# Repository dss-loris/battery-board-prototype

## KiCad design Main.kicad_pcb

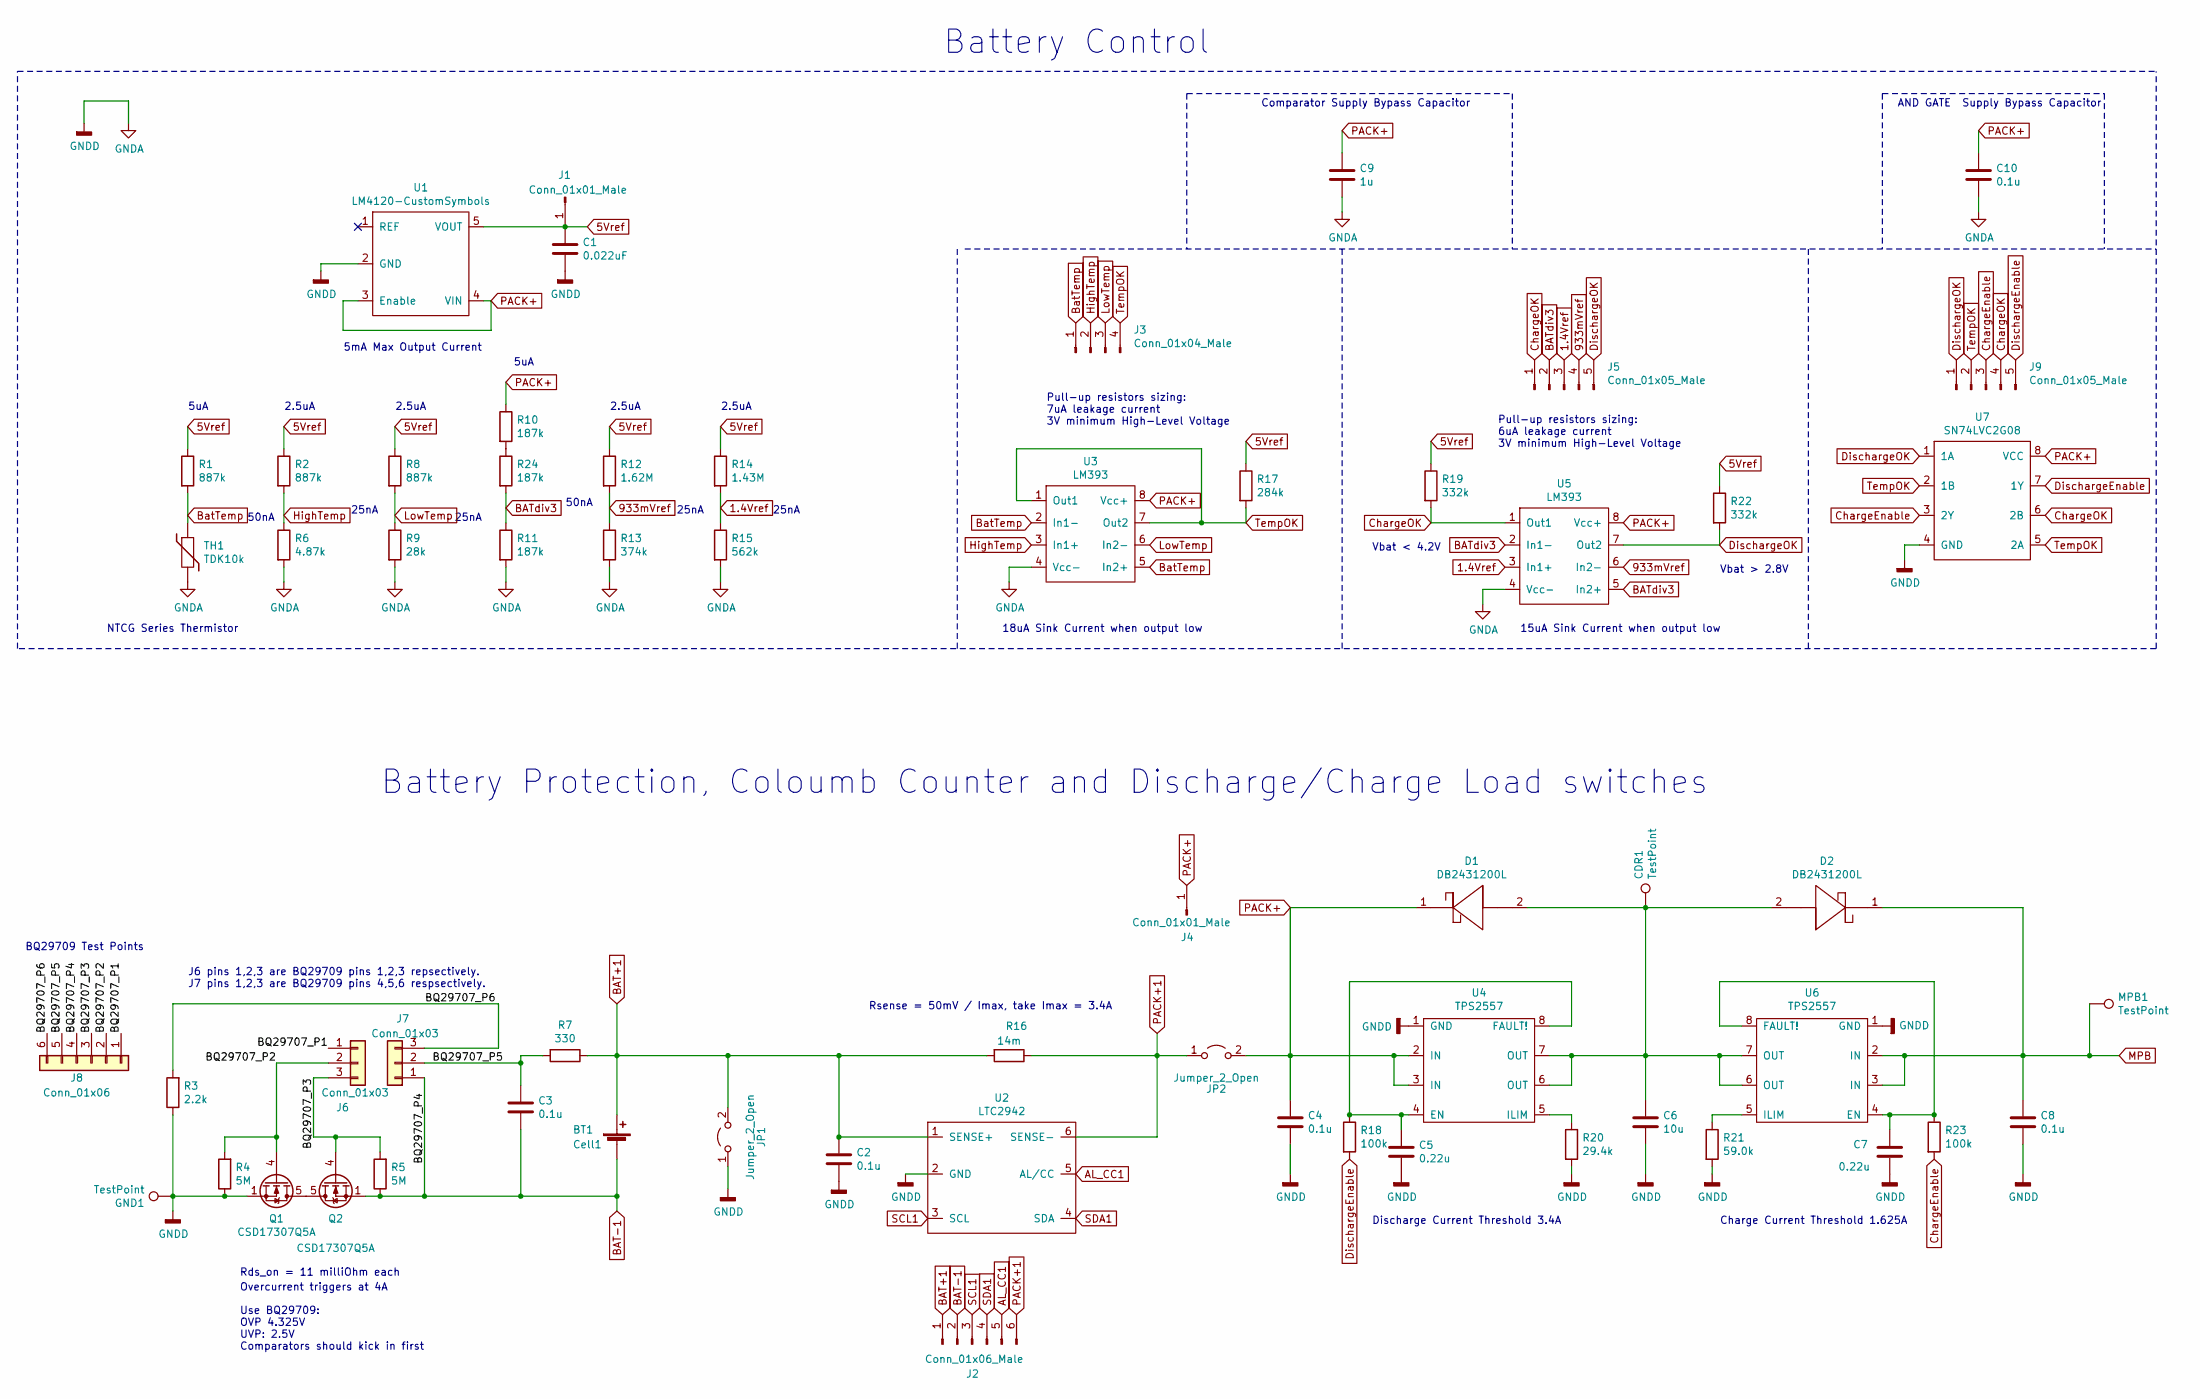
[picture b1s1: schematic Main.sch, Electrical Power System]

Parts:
BT1: Cell1; BatteryHolder_Keystone_1042_1x18650
C1: 0.022uF; C_1206_3216Metric_Pad1.42x1.75mm_HandSolder
C2, C3, C4, C8, C10: 0.1u; C_1206_3216Metric_Pad1.42x1.75mm_HandSolder
C5, C7: 0.22u; C_1206_3216Metric_Pad1.42x1.75mm_HandSolder
C6: 10u; C_1206_3216Metric_Pad1.42x1.75mm_HandSolder
C9: 1u; C_1206_3216Metric_Pad1.42x1.75mm_HandSolder
CDR1: TestPoint; PinHeader_1x01_P2.00mm_Vertical
D1, D2: DB2431200L
GND1: TestPoint; PinHeader_1x01_P2.00mm_Vertical
J1, J4: Conn_01x01_Male; PinHeader_1x01_P2.00mm_Vertical
J2: Conn_01x06_Male; PinSocket_1x06_P2.00mm_Vertical
J3: Conn_01x04_Male; PinHeader_1x04_P2.00mm_Vertical
J5, J9: Conn_01x05_Male; PinHeader_1x05_P2.00mm_Vertical
J6, J7: Conn_01x03; PinSocket_1x03_P2.54mm_Vertical
J8: Conn_01x06; PinHeader_1x06_P2.00mm_Vertical
JP1, JP2: Jumper_2_Open; PinSocket_1x01_P2.54mm_Vertical
MPB1: TestPoint; PinHeader_1x01_P2.00mm_Vertical
Q1, Q2: CSD17307Q5A; TDSON-8-1
R1, R2, R8: 887k; R_1206_3216Metric_Pad1.42x1.75mm_HandSolder
R3: 2.2k; R_1206_3216Metric_Pad1.42x1.75mm_HandSolder
R4, R5: 5M; R_1206_3216Metric_Pad1.42x1.75mm_HandSolder
R6: 4.87k; R_1206_3216Metric_Pad1.42x1.75mm_HandSolder
R7: 330; R_1206_3216Metric_Pad1.42x1.75mm_HandSolder
R9: 28k; R_1206_3216Metric_Pad1.42x1.75mm_HandSolder
R10, R11, R24: 187k; R_1206_3216Metric_Pad1.42x1.75mm_HandSolder
R12: 1.62M; R_1206_3216Metric_Pad1.42x1.75mm_HandSolder
R13: 374k; R_1206_3216Metric_Pad1.42x1.75mm_HandSolder
R14: 1.43M; R_0805_2012Metric_Pad1.15x1.40mm_HandSolder
R15: 562k; R_1206_3216Metric_Pad1.42x1.75mm_HandSolder
R16: 14m; R_0805_2012Metric
R17: 284k; R_0603_1608Metric_Pad1.05x0.95mm_HandSolder
R18, R23: 100k; R_1206_3216Metric_Pad1.42x1.75mm_HandSolder
R19, R22: 332k; R_1206_3216Metric_Pad1.42x1.75mm_HandSolder
R20: 29.4k; R_1206_3216Metric_Pad1.42x1.75mm_HandSolder
R21: 59.0k; R_1206_3216Metric_Pad1.42x1.75mm_HandSolder
TH1: TDK10k; R_0402_1005Metric
U1: LM4120-CustomSymbols; SOT-23-5_HandSoldering
U2: LTC2942; DFN-6-1EP_3x2mm_P0.5mm_EP1.65x1.35mm
U3, U5: LM393; SOIC-8-1EP_3.9x4.9mm_P1.27mm_EP2.29x3mm
U4, U6: TPS2557
U7: SN74LVC2G08; SN74LVC2G08DCTR

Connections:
1.4Vref: J5.3, R14.2, R15.1, U5.3 (In1+)
5Vref: C1.1, J1.1, R1.1, R2.1, R8.1, R12.1, R14.1, R17.1, R19.1, R22.1, U1.5 (VOUT)
933mVref: J5.4, R12.2, R13.1, U5.6 (In2-)
/BQ29707_P1: J6.1, J8.1
/BQ29707_P2: J6.2, J8.2, Q1.4 (G), R4.2
/BQ29707_P3: J6.3, J8.3, Q2.4 (G), R5.2
/BQ29707_P5: C3.1, J7.2, J8.5, R7.2
/BQ29707_P6: J7.3, J8.6, R3.2
AL_CC1: J2.5, U2.5 (AL/CC)
BAT+1: BT1.1 (+), C2.1, J2.1, JP1.2 (B), R7.1, R16.2, U2.1 (SENSE+)
BAT-1: BT1.2 (-), C3.2, J2.2, J7.1, J8.4, Q2.1 (S), Q2.2 (S), Q2.3 (S), R5.1
BATdiv3: J5.2, R11.1, R24.2, U5.2 (In1-), U5.5 (In2+)
BatTemp: J3.1, R1.2, TH1.1, U3.2 (In1-), U3.5 (In2+)
ChargeEnable: J9.3, R23.2, U7.3 (2Y)
ChargeOK: J5.1, J9.4, R19.2, U5.1 (Out1), U7.6 (2B)
DischargeEnable: J9.5, R18.2, U7.7 (1Y)
DischargeOK: J5.5, J9.1, R22.2, U5.7 (Out2), U7.1 (1A)
GNDA: C1.2, C2.2, C4.2, C5.2, C6.2, C7.2, C8.2, C9.2, C10.2, GND1.1, JP1.1 (A), Q1.1 (S), Q1.2 (S), Q1.3 (S), R3.1, R4.1, R6.2, R9.2, R11.2, R13.2, R15.2, R20.2, R21.2, TH1.2, U1.2 (GND), U2.2 (GND), U3.4 (Vcc-), U4.1 (GND), U5.4 (Vcc-), U6.1 (GND), U7.4 (GND)
HighTemp: J3.2, R2.2, R6.1, U3.3 (In1+)
LowTemp: J3.3, R8.2, R9.1, U3.6 (In2-)
MPB: C8.1, D2.1, MPB1.1, U6.2 (IN), U6.3 (IN)
unnamed: C5.1, R18.1, U4.4 (EN), U4.8 (FAULT!)
unnamed: C6.1, CDR1.1, D1.2, D2.2, U4.6 (OUT), U4.7 (OUT), U6.6 (OUT), U6.7 (OUT)
unnamed: C7.1, R23.1, U6.4 (EN), U6.8 (FAULT!)
unnamed: Q1.5 (D), Q2.5 (D)
unnamed: R10.2, R24.1
unnamed: R20.1, U4.5 (ILIM)
unnamed: R21.1, U6.5 (ILIM)
PACK+: C4.1, C9.1, C10.1, D1.1, J4.1, JP2.2 (B), R10.1, U1.3 (Enable), U1.4 (VIN), U3.8 (Vcc+), U4.2 (IN), U4.3 (IN), U5.8 (Vcc+), U7.8 (VCC)
PACK+1: J2.6, JP2.1 (A), R16.1, U2.6 (SENSE-)
SCL1: J2.3, U2.3 (SCL)
SDA1: J2.4, U2.4 (SDA)
TempOK: J3.4, J9.2, R17.2, U3.1 (Out1), U3.7 (Out2), U7.2 (1B), U7.5 (2A)

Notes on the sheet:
Rds_on = 11 milliOhm each
Overcurrent triggers at 4A
Discharge Current Threshold 3.4A
Charge Current Threshold 1.625A
2.5uA
5uA
25nA
50nA
5mA Max Output Current
NTCG Series Thermistor
Vbat > 2.8V
Vbat < 4.2V
Use BQ29709: OVP 4.325V UVP: 2.5V Comparators should kick in first
Pull-up resistors sizing: 6uA leakage current 3V minimum High-Level Voltage
Pull-up resistors sizing: 7uA leakage current 3V minimum High-Level Voltage
18uA Sink Current when output low
15uA Sink Current when output low
Comparator Supply Bypass Capacitor
AND GATE Supply Bypass Capacitor
Battery Control
Battery Protection, Coloumb Counter and Discharge/Charge Load switches
BQ29709 Test Points
Rsense = 50mV / Imax, take Imax = 3.4A
J6 pins 1,2,3 are BQ29709 pins 1,2,3 repsectively. J7 pins 1,2,3 are BQ29709 pins 4,5,6 respsectively.

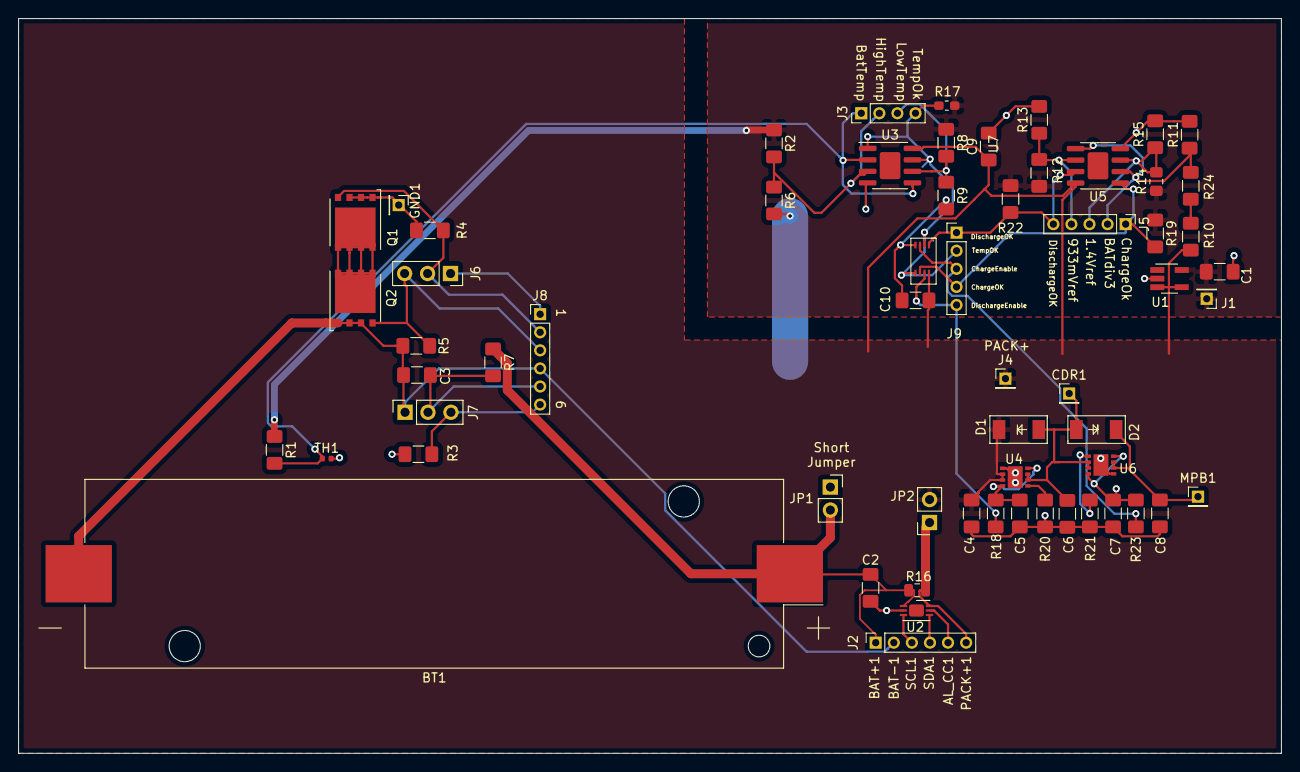
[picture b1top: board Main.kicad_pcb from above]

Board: 2 copper layers, 139.7 x 81.3 mm, 61 parts (0 on the bottom side), 33 nets.

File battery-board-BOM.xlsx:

Index | Quantity | Part Number | Manufacturer Part Number | Description | Customer Reference | Available | Backorder | Unit Price | Extended Price USD
1 | 4 | DB2431200LCT-ND | DB2431200L | DIODE SCHOTTKY 30V 5A TMINIP2 | D1,D2 … BB | 4 | 0 | 0.42 | 1.68
2 | 2 | 2057-2PH1-05-UA-ND | 2PH1-05-UA | CONN HEADER VERT 5POS 2MM | J5,J9 … BB | 2 | 0 | 0.18 | 0.36
3 | 2 | 2057-2PH1-04-UA-ND | 2PH1-04-UA | CONN HEADER VERT 4POS 2MM | J3 … BB | 2 | 0 | 0.14000000000000001 | 0.28000000000000003
4 | 2 | 952-1316-ND | M22-2511005 | CONN HEADER VERT 10POS 2MM | J1,J4,CDR1,GND1,MPB1 … BB | 2 | 0 | 0.61 | 1.22
5 | 2 | LM4120AIM5-5.0/NOPBCT-ND | LM4120AIM5-5.0/NOPB | IC VREF SERIES 0.2% SOT23-5 | U1 … BB | 2 | 0 | 2.19 | 4.38
6 | 2 | WM4000-ND | 0022032021 | CONN HEADER VERT 2POS 2.54MM | JP1,JP2 … BB | 2 | 0 | 0.25 | 0.5
7 | 10 | 399-C1206C104K5RAC7800CT-ND | C1206C104K5RAC7800 | CAP CER 0.1UF 50V X7R 1206 | C2,C3,C4,C8,10 … BB | 10 | 0 | 8.7999999999999995E-2 | 0.88
8 | 2 | 1849-1001-ND | PR20C06VBNN | CONN HEADER VERT 6POS 2MM | J2,J8 … BB | 2 | 0 | 0.16 | 0.32
9 | 2 | 399-8150-1-ND | C1206C105M4RACTU | CAP CER 1UF 16V X7R 1206 | C9 … BB | 2 | 0 | 0.19 | 0.38
10 | 3 | 408-2038-1-ND | RG3216P-5004-B-T1 | RES 5M OHM 0.1% 1/4W 1206 | R4,R5 … BB | 3 | 0 | 0.76 | 2.2799999999999998
11 | 1 | 36-1042-ND | 1042 | BATTERY HOLDER 18650 SMD TAB | BT1 … BB | 1 | 0 | 2.76 | 2.76
12 | 2 | 399-9329-1-ND | C1206C223J1RACTU | CAP CER 0.022UF 100V X7R 1206 | C1 … BB | 2 | 0 | 0.2 | 0.4
13 | 3 | 399-1251-1-ND | C1206C224K5RACTU | CAP CER 0.22UF 50V X7R 1206 | C5,C7 … BB | 3 | 0 | 0.23 | 0.69
14 | 2 | 311-2007-1-ND | CC1206ZRY5V6BB106 | CAP CER 10UF 10V Y5V 1206 | C6 … BB | 2 | 0 | 0.23 | 0.46
15 | 3 | 732-5316-ND | 61300311121 | CONN HEADER VERT 3POS 2.54MM | J6,J7 … BB | 3 | 0 | 0.13 | 0.39
16 | 5 | RG32P887KBCT-ND | RG3216P-8873-B-T1 | RES SMD 887K OHM 0.1% 1/4W 1206 | R1,R2,R8 … BB | 5 | 0 | 0.68 | 3.4
17 | 2 | P2.2KECT-ND | ERJ-8GEYJ222V | RES SMD 2.2K OHM 5% 1/4W 1206 | R3 … BB | 2 | 0 | 0.1 | 0.2
18 | 2 | P4.87KFCT-ND | ERJ-8ENF4871V | RES SMD 4.87K OHM 1% 1/4W 1206 | R6 … BB | 2 | 0 | 0.1 | 0.2
19 | 2 | P330FCT-ND | ERJ-8ENF3300V | RES SMD 330 OHM 1% 1/4W 1206 | R7 … BB | 2 | 0 | 0.1 | 0.2
20 | 2 | RNCP1206FTD28K0CT-ND | RNCP1206FTD28K0 | RES 28K OHM 1% 1/2W 1206 | R9 … BB | 2 | 0 | 0.1 | 0.2
21 | 4 | P332KFCT-ND | ERJ-8ENF3323V | RES SMD 332K OHM 1% 1/4W 1206 | R19,R22 … BB | 4 | 0 | 0.1 | 0.4
22 | 5 | P187KBCCT-ND | ERA-8AEB1873V | RES SMD 187K OHM 0.1% 1/4W 1206 | R0,R11,R24 … BB | 5 | 0 | 0.66 | 3.3
23 | 2 | 311-1.62MFRCT-ND | RC1206FR-071M62L | RES SMD 1.62M OHM 1% 1/4W 1206 | R12 … BB | 2 | 0 | 0.1 | 0.2
24 | 2 | P374KFCT-ND | ERJ-8ENF3743V | RES SMD 374K OHM 1% 1/4W 1206 | R13 … BB | 2 | 0 | 0.1 | 0.2
25 | 2 | RMCF0805FT1M43CT-ND | RMCF0805FT1M43 | RES 1.43M OHM 1% 1/8W 0805 | R14 … BB | 2 | 0 | 0.1 | 0.2
26 | 2 | P562KFCT-ND | ERJ-8ENF5623V | RES SMD 562K OHM 1% 1/4W 1206 | R15 … BB | 2 | 0 | 0.1 | 0.2
27 | 2 | WSLPB-.014CT-ND | WSLP0805R0140FEB | RES 0.014 OHM 1% 1/2W 0805 | R16 … BB | 2 | 0 | 1.27 | 2.54
28 | 2 | RR08P284KDCT-ND | RR0816P-2843-D-E00 | RES SMD 284K OHM 0.5% 1/16W 0603 | R17 … BB | 2 | 0 | 0.13 | 0.26
29 | 3 | P100KFCT-ND | ERJ-8ENF1003V | RES SMD 100K OHM 1% 1/4W 1206 | R18,R23 … BB | 3 | 0 | 0.1 | 0.3
30 | 2 | P29.4KFCT-ND | ERJ-8ENF2942V | RES SMD 29.4K OHM 1% 1/4W 1206 | R20 … BB | 2 | 0 | 0.1 | 0.2
31 | 2 | P59.0KFCT-ND | ERJ-8ENF5902V | RES SMD 59K OHM 1% 1/4W 1206 | R21 … BB | 2 | 0 | 0.1 | 0.2
32 | 2 | 445-174306-1-ND | NTCG103JX103DT1 | THERMISTOR NTC 10KOHM 3380K 0402 | TH1 … BB | 2 | 0 | 0.23 | 0.46
33 | 4 | 296-25857-1-ND | CSD17307Q5A | MOSFET N-CH 30V 73A 8SON | Q1,Q2 … BB | 4 | 0 | 0.76 | 3.04
34 | 2 | LTC2942CDCB#TRMPBFCT-ND | LTC2942CDCB#TRMPBF | IC FUEL/GAS GAUGE LI-ION 6DFN | U2 … BB | 2 | 0 | 3.86 | 7.72
35 | 4 | 296-37669-6-ND | TPS2557DRBR | IC PWR SWITCH N-CHAN 1:1 8SON | U4,U6 … BB | 4 | 0 | 3.89 | 15.56
36 | 2 | 296-13263-1-ND | SN74LVC2G08DCTR | IC GATE AND 2CH 2-INP SM8 | U7 … BB | 2 | 0 | 0.54 | 1.08
37 | 5 | 296-1015-1-ND | LM393DR | IC DUAL DIFF COMP 8-SOIC | U3,U5 … BB | 5 | 0 | 0.38 | 1.9
38 | 5 | 15291025 | 0015291025 | CONN SHUNT CLOSED TOP .100 GOLD | JUMPERS … BB | 5 | 0 | 0.56000000000000005 | 2.8
39 | 4 | 296-39948-1-ND | BQ29707DSER | IC LITHIUM BATT PROTECT 6WSON | BQ29707 … BB | 4 | 0 | 0.69 | 2.76

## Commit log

2019-12-05 changed_resistor
2019-12-05 annotated schematic
2019-12-05 Added footprints for symbols, need to find schottkys
2019-12-05 started layout
2019-12-05 added txt
2019-12-05 Changed Comparator supply to Pack+. Changed pull-up resistor supply from Pack to 5Vref, changed values of pull-up resistors.
2019-12-07 worked on pcb
2019-12-10 restarted
2019-12-11 progress
2019-12-12 changed test points
2019-12-13 removed_switches
2019-12-13 u-slot
2019-12-16 done
2019-12-18 changed_footprings
2020-01-07 gerbers
2020-01-07 added_bom
